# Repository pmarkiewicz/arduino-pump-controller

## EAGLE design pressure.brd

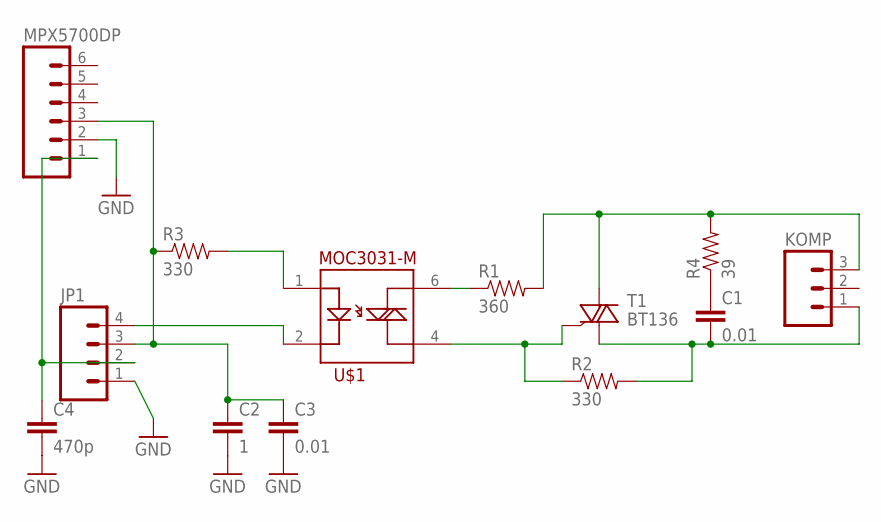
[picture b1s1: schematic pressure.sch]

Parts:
C1, C3: 0.01; CAP-PTH-5MM
C2: 1; CAP-PTH-5MM
C4: 470p; CAP-PTH-5MM
JP1: M04LONGPADS; 1X04_LONGPADS
KOMP: M03LONGPADS; 1X03_LONGPADS
MPX5700DP: M06LONGPADS; 1X06_LONGPADS
R1: 360; AXIAL-0.3-KIT
R2, R3: 330; AXIAL-0.3-KIT
R4: 39; AXIAL-0.3-KIT
T1: BT136; TO220AB
U$1: MOC3031-M; DIL06

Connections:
GND: C2.2, C3.2, C4.2, JP1.1, MPX5700DP.2
KOMP: KOMP.3, R1.P$2 (2), R4.P$2 (2), T1.2 (A2)
unnamed: C1.2, KOMP.1, R2.P$2 (2), T1.1 (A1)
unnamed: R2.P$1 (1), T1.3 (G), U$1.4
unnamed: C2.1, C3.1, JP1.3, MPX5700DP.3, R3.P$1 (1)
unnamed: R3.P$2 (2), U$1.1
unnamed: JP1.4, U$1.2
unnamed: R1.P$1 (1), U$1.6
unnamed: C4.1, JP1.2, MPX5700DP.1
unnamed: C1.1, R4.P$1 (1)

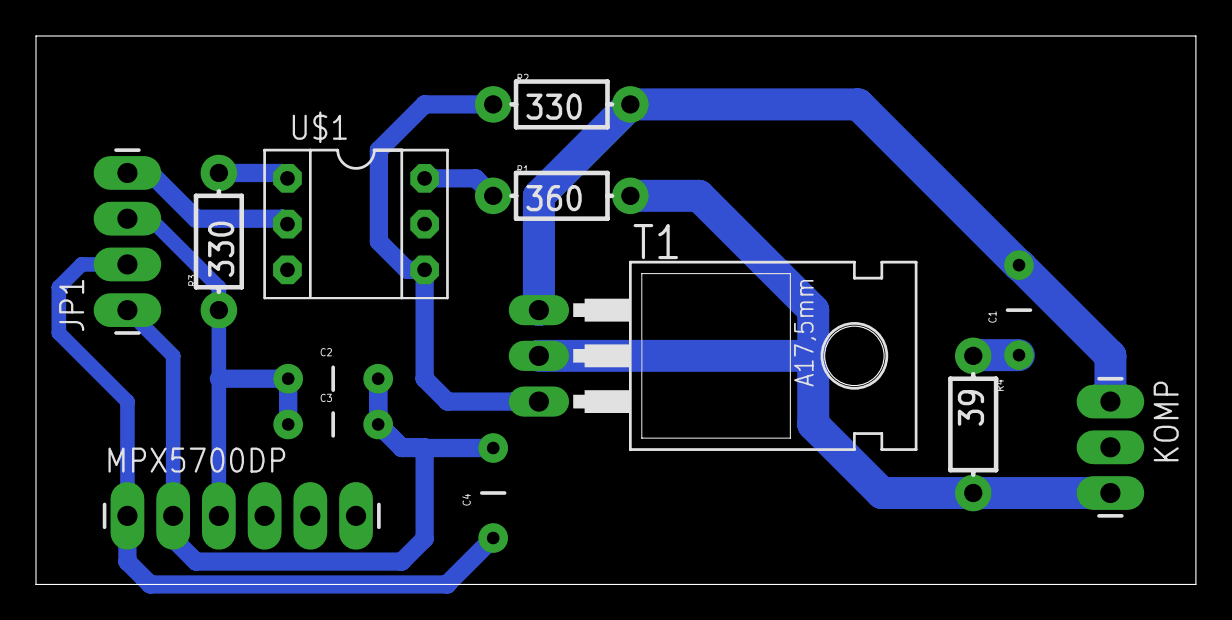
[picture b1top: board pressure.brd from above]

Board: 2 copper layers, 64.4 x 30.5 mm, 13 parts (0 on the bottom side), 10 nets.

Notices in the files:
parts and their libraries:
SparkFun-DiscreteSemi: Licensing: CC v3.0 Share-Alike You are welcome to use this library for commercial purposes.
